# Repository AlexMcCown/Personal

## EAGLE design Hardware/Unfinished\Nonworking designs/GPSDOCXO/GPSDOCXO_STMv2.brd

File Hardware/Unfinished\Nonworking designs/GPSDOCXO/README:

Im starting to upload old designs that i never finished.
This is an GPSDOCXO or GPS Disciplined Oven-Controlled crystal(X) Oscillator to be used as a 10MHz lab reference.
The basic design is simple, a good oven-controlled crystal oscillator like the double oven used here is capable of drift and jitter down in the parts per billion but is not very accurate
A GPS based time reference is extremely accurate but not at a usable frequency.
GPSDOCXO's are designed to lock an OCXO to a timing GPS.

My concept was a mix of a PLL (phase locked loop) and a FLL (frequency locked loop) with the basic concept working in 2 stages.
Stage 1 is the FLL stage, we lock the OCXO to the 1 PPS (pulse per second) signal of the GPS, we start by counting the number of pulses the OCXO puts out between 2 rising edges of the GPS PPS.
We adjust our OCXO using a look up table or formula to match the desired frequency and try again, once thats locked we increase our gate time to 10 pulses, and count.
we continue this for as much as a 425 gates (or roughly 7 minutes) and adjust.
Once we have reached lock we can slowly skew the OCXO until we are right on the edge of going one count over, this will keep our phases locked.
As double oven OCXOs should never be turned off once burned in, this long startup time is fine.

The hardware is fairly simple, we convert the sine wave from the OCXO to a square wave using a TLV3501 4.5-ns compactor, that is fed in to a PL123-05N clock distribution chip that
claims 60fs of RMS jitter. The output of that is split in to 3 usable output ports (2 of them are 50 ohm buffered) with one going to a MAXII CPLD (Complex programmable logic device)
that handles the counting and reports the count offset (no need to report the full count as it will be close enough) to an STM32F402CC based USB module, that module controls a 
DACx0501 (i indend to use a DAC80501 here) that has a 5-ppm/˚C class voltage reference built in. 
The GPS used is a Ublox LEA-5T-0-003 based timing GPS module thats avalable on ebay for under $20 removed from huawei 4G cell towers.
These modules are very nice as they come with built in TVS suppressors, antenna power injection and over current detection.
This whole design was designed to fit in to standard aluminum extrusion cases.

There are plenty of issues with this design. First of all the CPLD code is rough and unfinished. The 2 layer PCB was a pipe-dream and is simply too few layers for this sort of design
in this sort of size.
The OCXO unit will need to be placed in a separate box as the unit it self can easily hit 50*C and bake everything inside.
There is no on board primary power supply.
There is a bottleneck somewhere in the design but without building it im not sure where it is. Obviously this is not 100% perfectly accurate and precise of a 10MHz time reference 
something has to be the bottleneck.  If the bottleneck is the OCXO or the GPS we can reduce part cost. Either use cheaper clock distributors, a lower resolution DAC or using a
single cheap FPGA to replace the microcontroller entirely. Normally i will create a design with the best chips i can than reduce part specifications until we approch our bottleneck.
Having a GPS on board means that this design is ideal for not just being a GPSDOCXO but also an NTP server, using a microcontroller with ethernet like an LPC1768 might be a better
solution.
a single 5v line on the PCB is unconnected and a re-layout of the upper right section is required.
The STM32F402CC board is not a standard blackpill and does not have an easy name to reference people to.
The STM32F402CC is only used for its USB and Floating point unit.
There is no font panel PCB but the intention was 5 buttons and an OLED display.

I might come back to this design but with access to a high precision atomic frequency counter, simply using my OCXO as a routinely calabrated unit is good enough for my home use.

The CPLD code is written in verilog, does not include a functional Shift-Out register and was the first time i have written anything in verilog. The only solution i could come up with
for the problem of resetting a counter while continiously counting was to create 2 counters.  This should all fit in the smallest MAX II CPLD so i left it like that.
There is an external GPIO interface intended for a distribution box, Internal header intended for an FTP server, The front RS232 is for standard NMEA output, configuration or the FTP
depending on jumper configurations.

EDIT: There is no code for the STM32F402CC.  I started writing it in C++ than switched over to platformio/arduino and chose to stop until i had the actual hardware in hand.
If i can find any of it i will upload both here.  The only thing i implemented were some test scripts to write to the CPLD and read, controlling the DAC and reading from the GPS.

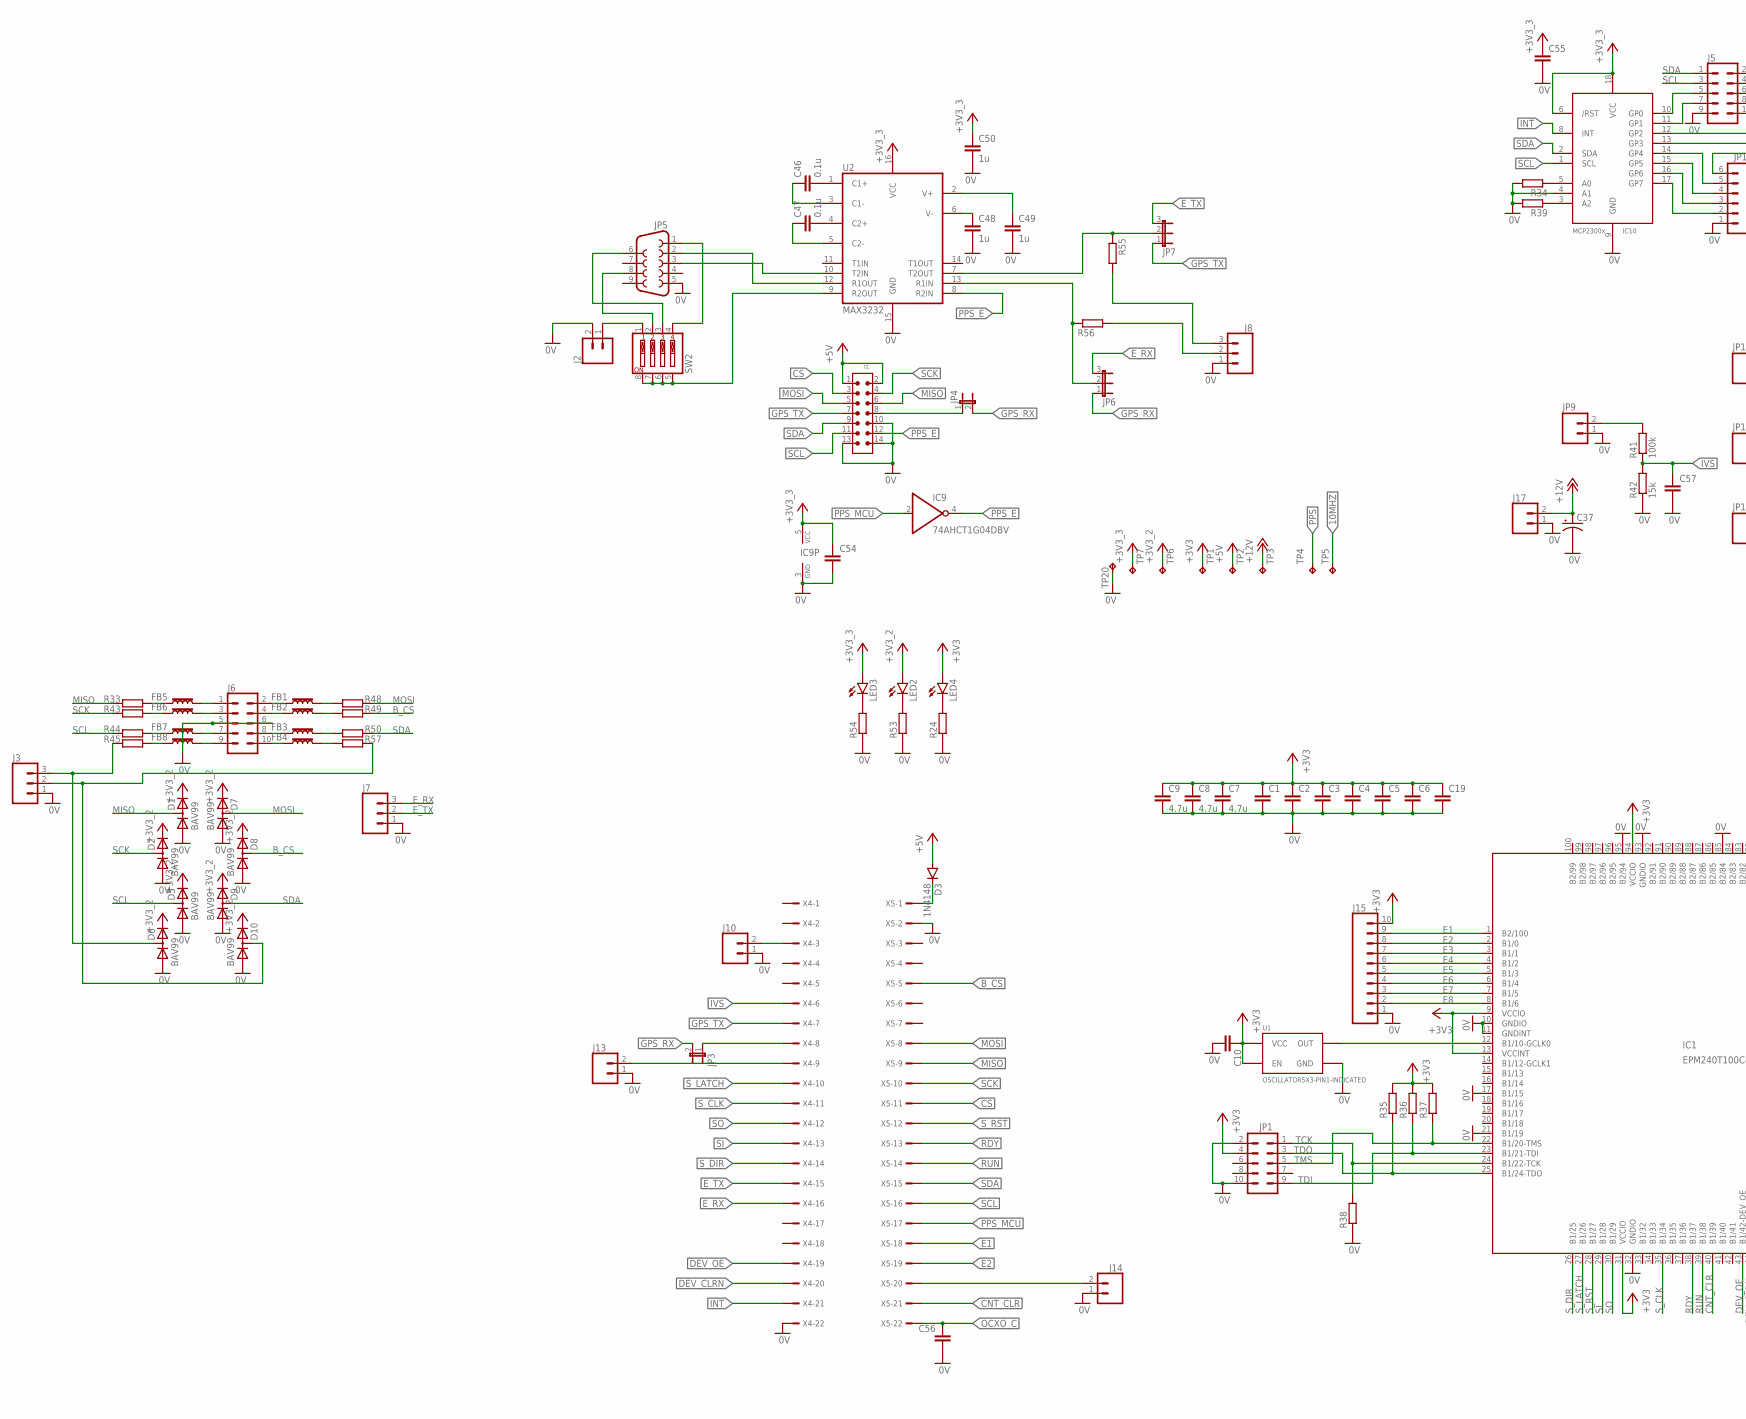
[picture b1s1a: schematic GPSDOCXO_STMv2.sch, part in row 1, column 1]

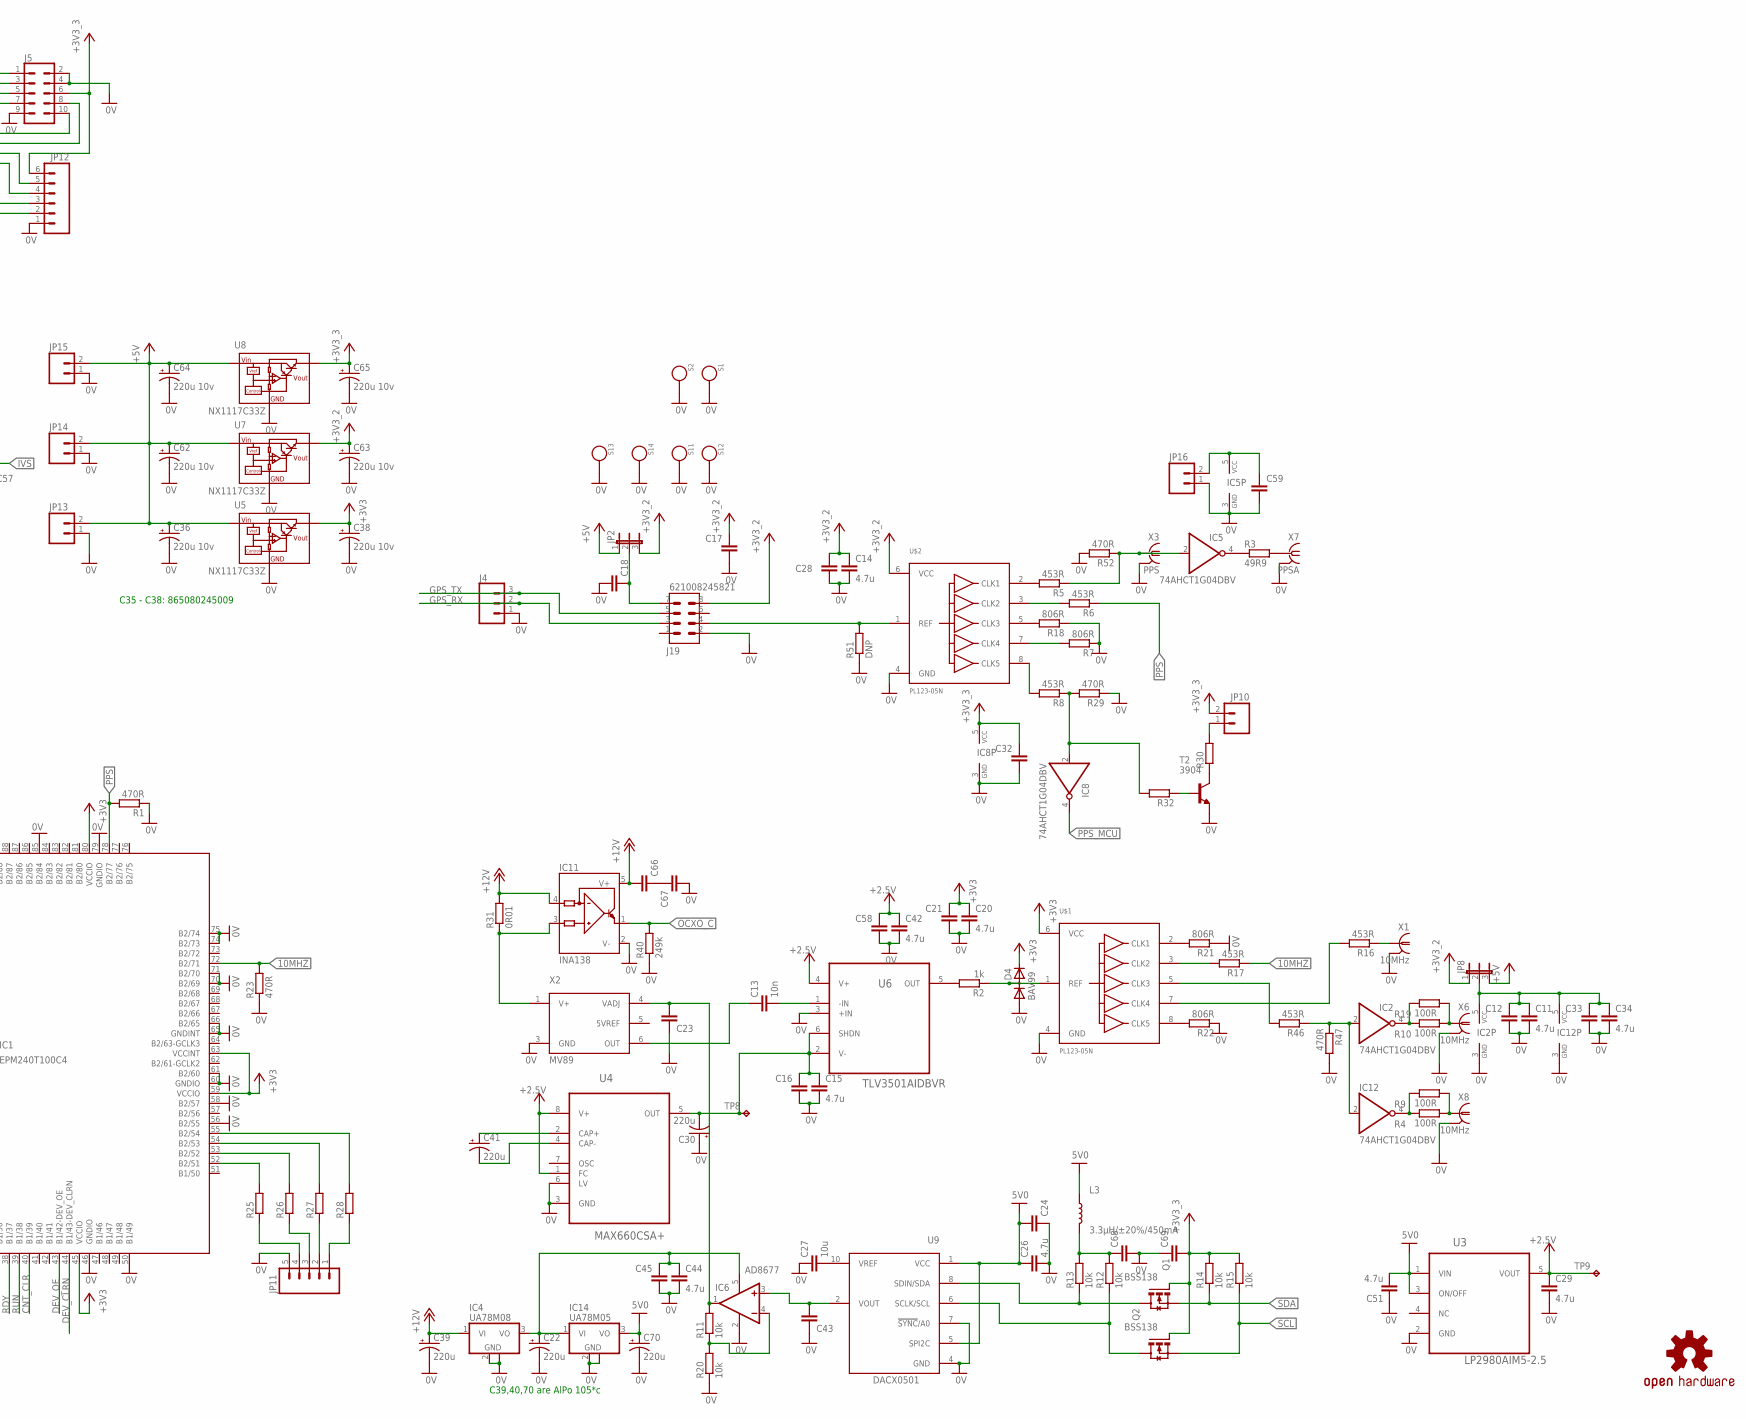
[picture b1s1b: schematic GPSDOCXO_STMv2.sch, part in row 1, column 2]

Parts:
C1, C2, C3, C4, C5, C6, C10, C12, C16, C19, C21, C23, C24, C28, C32, C33, C43, C45, C54, C55, C56, C57, C58, C59, C66, C67, C68, C69: C-EUC0603; C0603
C7, C8, C9, C11, C14, C15, C20, C26, C29, C34, C42, C44, C51: 4.7u; C0805
C13: 10n; C0805
C17, C18: C-EUC0805; C0805
C22, C70: 220u; 153CLV-0605
C27: 10u; C0805
C30, C39, C41: 220u; 153CLV-1010
C36, C38, C62, C63, C64, C65: 220u 10v; 153CLV-0605
C37: CPOL-USE3.5-8; E3,5-8
C46, C47: 0.1u; C0603
C48, C49, C50: 1u; C0603
D1, D2, D4, D5, D6, D7, D8, D9, D10: BAV99; SOT23
D3: 1N4148; DO35-7
FB1, FB2, FB3, FB4, FB5, FB6, FB7, FB8: FERRITE_BEAD-0603; 0603
IC1: EPM240T100C4; TQFP100
IC2, IC5, IC8, IC9, IC12: 74AHCT1G04DBV; SOT23-5
IC4: UA78M08; SOT223
IC6: AD8677; SOT23-5
IC10: MCP23008/SO; SO18W
IC11: INA138; SOT23-5
IC14: UA78M05; SOT223
J1: 6120XX21621_61201421621; 61201421621
J2, J10, J13, J14: CONN_02; 1X02
J3, J7, J8: M03POLAR; MOLEX-1X3
J4: CONN_03; 1X03
J5: CONN_05X2SHD-NS; 2X5-SHROUDED-NS
J6: CONN_05X2RAF; 2X5-RAF
J15: CONN_10NO_SILK_PTH_FEMALE; 1X10_NO_SILK
J17: CONN_025MM; SCREWTERMINAL-5MM-2
J19: 621008245821
JP1: M05X2SHD-NS; 2X5-SHROUDED-NS
JP2, JP6, JP7, JP8: JP2E; JP2
JP3, JP4: JP1E; JP1
JP5: DB9FEMALE; DB9
JP9, JP10, JP13, JP14, JP15, JP16: M02POLAR; MOLEX-1X2
JP11: M05NO_SILK; 1X05_NO_SILK
JP12: M06SILK_FEMALE_PTH; 1X06
L3: 3.3µH/±20%/450mA; 0805
LED2, LED3, LED4: LED5MM
LOGO1: OSHW-LOGOL; OSHW-LOGO-L
Q1, Q2: BSS138; SOT23-3
R1, R23, R29, R47, R52: 470R; R0603
R2: 1k; R0603
R3: 49R9; R0805
R4, R9, R10, R19: 100R; R0805
R5, R6, R8, R16, R17, R46: 453R; R0603
R7, R18, R21, R22: 806R; R0603
R11, R12, R13, R14, R15, R20: 10k; R0603
R24, R25, R26, R27, R28, R30, R32, R33, R34, R35, R36, R37, R38, R39, R43, R44, R45, R48, R49, R50, R53, R54, R55, R56, R57: R-EU_R0603; R0603
R31: 0R01; R1210
R40: 249k; R0603
R41: 100k; 0204/7
R42: 15k; R0603
R51: DNP; R0603
S1, S2, S11, S12, S13, S14: STANDOFF_ELECTRICAL; STANDOFF-ELECTRICAL
SW2: SW_DIP-4; EDG-04
T2: 3904; SOT23-BEC
TP1, TP2, TP3, TP6, TP7, TP8, TP9, TP20: TPPAD1-13; P1-13
TP4, TP5: TPTP13R; TP13R
U1: OSCILLATOR5X3-PIN1-INDICATED; CRYSTAL-OSC-SMD-5X3
U2: MAX3232; SO16
U3: LP2980AIM5-2.5; SOT95P284X119-5N
U4: MAX660CSA+; SOIC127P600X175-8N
U5, U7, U8: NX1117C33Z; SOT223
U6: TLV3501AIDBVR; SOT95P280X145-6N
U9: DACX0501; VSSOP-10
U$1, U$2: PL123-05N; SOIC-8
X1, X6, X8: 10MHz; AMP_227161
X2: MV89
X3: PPS; BU-SMA-V
X4, X5: TSW-122-07-G-S; TSW-122-XX-G-S
X7: PPSA; BU-SMA-V

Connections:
0V: C1.2, C2.2, C3.2, C4.2, C5.2, C6.2, C7.2, C8.2, C9.2, C10.2, C11.2, C12.2, C14.2, C15.2, C16.2, C17.2, C18.2, C19.2, C20.2, C21.2, C22.-, C23.1, C24.1, C26.2, C27.1, C28.2, C29.2, C30.+, C32.2, C33.2, C34.2, C36.-, C37.-, C38.-, C39.-, C42.2, C43.1, C44.2, C45.2, C48.2, C49.2, C50.2, C51.1, C54.2, C55.2, C56.2, C57.2, C58.2, C59.2, C62.-, C63.-, C64.-, C65.-, C67.2, C68.1, C69.2, C70.-, D1.1 (A1), D2.1 (A1), D4.1 (A1), D5.1 (A1), D6.1 (A1), D7.1 (A1), D8.1 (A1), D9.1 (A1), D10.1 (A1), IC1.10 (GNDIO), IC1.11 (GNDINT), IC1.17 (B1/15), IC1.21 (B1/19), IC1.32 (GNDIO), IC1.46 (GNDIO), IC1.50 (B1/49), IC1.56 (B2/55), IC1.58 (B2/57), IC1.60 (GNDIO), IC1.61 (B2/60), IC1.65 (GNDINT), IC1.66 (B2/65), IC1.70 (B2/69), IC1.71 (B2/70), IC1.74 (B2/73), IC1.75 (B2/74), IC1.79 (GNDIO), IC1.85 (B2/84), IC1.93 (GNDIO), IC1.95 (B2/94), IC2.3 (GND), IC4.2 (GND), IC4.4 (GND), IC5.3 (GND), IC6.2 (V-), IC8.3 (GND), IC9.3 (GND), IC10.4 (A1), IC10.9 (GND), IC11.2 (V-), IC12.3 (GND), IC14.2 (GND), IC14.4 (GND), J1.10, J1.13, J1.14, J2.2, J3.1, J4.1, J5.2, J5.4, J5.9, J6.5, J6.6, J7.1, J8.1, J10.1, J13.1, J14.1, J15.1, J17.1, J19.2, JP1.2, JP1.10, JP5.5, JP9.1, JP11.5, JP12.1, JP13.1, JP14.1, JP15.1, JP16.1, R1.1, R7.1, R18.1, R20.1, R21.1, R22.1, R23.1, R24.1, R29.1, R34.2, R38.1, R39.2, R40.1, R42.1, R47.2, R51.1, R52.2, R53.1, R54.1, S1.P1, S2.P1, S11.P1, S12.P1, S13.P1, S14.P1, T2.E, TP20.TP, U1.2 (GND), U2.15 (GND), U3.2 (GND), U4.3 (GND), U4.6 (LV), U5.1 (GND), U6.3 (+IN), U7.1 (GND), U8.1 (GND), U9.4 (GND), U9.7 (!SYNC!/A0), U$1.4 (GND), U$2.4 (GND), X1.2, X2.3 (GND), X3.2, X3.3 (2), X3.4 (2), X3.5 (2), X4.22, X5.2, X6.2, X7.2, X7.3 (2), X7.4 (2), X7.5 (2), X8.2
10MHZ: IC1.72 (B2/71), R17.1, R23.2, TP5.TP
+2V5: C29.1, C42.1, C58.1, TP9.TP, U3.5 (VOUT), U4.1 (FC), U4.8 (V+), U6.4 (V+)
+3V3: C1.1, C2.1, C3.1, C4.1, C5.1, C6.1, C7.1, C8.1, C9.1, C10.1, C19.1, C20.1, C21.1, C38.+, D4.2 (K2), IC1.9 (VCCIO), IC1.13 (VCCINT), IC1.31 (VCCIO), IC1.45 (VCCIO), IC1.59 (VCCIO), IC1.63 (VCCINT), IC1.80 (VCCIO), IC1.94 (VCCIO), J15.10, JP1.4, LED4.A, R35.2, R36.2, R37.2, TP1.TP, U1.1 (EN), U1.4 (VCC), U5.2 (VOUT), U5.4 (VOUT), U$1.6 (VCC)
+3V3_2: C14.1, C17.1, C28.1, C63.+, D1.2 (K2), D2.2 (K2), D5.2 (K2), D6.2 (K2), D7.2 (K2), D8.2 (K2), D9.2 (K2), D10.2 (K2), J19.8, JP2.3, JP8.1, LED2.A, TP6.TP, U7.2 (VOUT), U7.4 (VOUT), U$2.6 (VCC)
+3V3_3: C32.1, C50.1, C54.1, C55.1, C65.+, C69.1, IC8.5 (VCC), IC9.5 (VCC), IC10.6 (/RST), IC10.18 (VCC), J5.6, JP10.2, JP12.6, LED3.A, Q1.1 (G), Q2.1 (G), R14.2, R15.2, TP7.TP, U2.16 (VCC), U8.2 (VOUT), U8.4 (VOUT)
+5V: C36.+, C62.+, C64.+, D3.A, J1.1, J1.2, JP2.1, JP8.3, JP13.2, JP14.2, JP15.2, TP2.TP, U5.3 (VIN), U7.3 (VIN), U8.3 (VIN)
+12V: C37.+, C39.+, C66.2, IC4.1 (VI), IC11.4 (IN-), IC11.5 (V+), J17.2, R31.2, TP3.TP
+V: C24.2, C26.1, C51.2, C70.+, IC14.3 (VO), L3.1, U3.1 (VIN), U3.3 (ON/OFF), U9.1 (VCC), U9.5 (SPI2C)
B_CS: D8.3 (K1A2), R49.1, X5.5
CNT_CLR: IC1.40 (B1/39), X5.21
CS: J1.3, X5.11
DEV_CLRN: IC1.44 (B1/43-DEV_CLRN), X4.20
DEV_OE: IC1.43 (B1/42-DEV_OE), X4.19
E1: IC1.1 (B2/100), J15.9, X5.18
E2: IC1.2 (B1/0), J15.8, X5.19
E3: IC1.3 (B1/1), J15.7
E4: IC1.4 (B1/2), J15.6
E5: IC1.5 (B1/3), J15.5
E6: IC1.6 (B1/4), J15.4
E7: IC1.7 (B1/5), J15.3
E8: IC1.8 (B1/6), J15.2
E_RX: J7.3, JP6.3, X4.16
E_TX: J7.2, JP7.3, X4.15
GPS_RX: J4.2, J19.3, JP3.2, JP4.2, JP6.1
GPS_RX_AJ: JP3.1, X4.8
GPS_RX_AJ2: J1.8, JP4.1
GPS_TX: J1.7, J4.3, J19.5, JP7.1, X4.7
INT: IC10.8 (INT), X4.21
IVS: C57.1, R41.1, R42.2, X4.6
MISO: D1.3 (K1A2), J1.6, R33.1, X5.9
MOSI: D7.3 (K1A2), J1.5, R48.1, X5.8
unnamed: J13.2, X4.9
unnamed: JP9.2, R41.2
unnamed: J19.4, R51.2, U$2.1 (REF)
unnamed: R5.2, U$2.2 (CLK1)
unnamed: C13.2, U6.1 (-IN)
unnamed: C13.1, X2.6 (OUT)
unnamed: R21.2, U$1.2 (CLK1)
unnamed: JP7.2, R55.1, U2.7 (T2OUT)
unnamed: R6.2, U$2.3 (CLK2)
unnamed: R7.2, U$2.7 (CLK4)
unnamed: JP5.2, U2.12 (R1OUT)
unnamed: R18.2, U$2.5 (CLK3)
unnamed: R8.2, U$2.8 (CLK5)
unnamed: IC10.10 (GP0), J5.5
unnamed: R32.1, T2.B
unnamed: JP10.1, R30.2
unnamed: R30.1, T2.C
unnamed: R2.2, U6.5 (OUT)
unnamed: IC1.12 (B1/10-GCLK0), U1.3 (OUT)
unnamed: C23.2, IC6.1 (OUT), R11.2, X2.4 (VADJ)
unnamed: IC5.4 (O), R3.1
unnamed: C22.+, C44.1, C45.1, IC4.3 (VO), IC6.5 (V+), IC14.1 (VI)
unnamed: Q1.3 (D), R13.1, U9.8 (SDIN/SDA)
unnamed: IC12.4 (O), R4.1, R9.1
unnamed: IC5.2 (I), R5.1, R52.1, X3.1
unnamed: Q2.3 (D), R12.1, U9.6 (SCLK/SCL)
unnamed: R3.2, X7.1
unnamed: R4.2, R9.2, X8.1
unnamed: J8.2, R56.2
unnamed: C18.1, J19.7, JP2.2
unnamed: J10.2, X4.3
unnamed: C66.1, C67.1
unnamed: IC10.11 (GP1), J5.7
unnamed: IC10.12 (GP2), J5.10
unnamed: IC10.13 (GP3), J5.8
unnamed: IC10.16 (GP6), JP12.3
unnamed: R17.2, U$1.3 (CLK2)
unnamed: R46.2, U$1.5 (CLK3)
unnamed: IC10.14 (GP4), JP12.5
unnamed: IC10.15 (GP5), JP12.4
unnamed: IC10.17 (GP7), JP12.2
unnamed: IC10.5 (A0), R34.1
unnamed: LED4.K (C), R24.2
unnamed: JP11.4, R25.1
unnamed: IC10.3 (A2), R39.1
unnamed: JP11.3, R26.1
unnamed: JP11.2, R27.1
unnamed: JP11.1, R28.1
unnamed: IC1.52 (B2/51), R25.2
unnamed: IC1.53 (B2/52), R26.2
unnamed: IC1.54 (B2/53), R27.2
unnamed: IC1.55 (B2/54), R28.2
unnamed: IC2.2 (I), IC12.2 (I), R46.1, R47.1
unnamed: C11.1, C12.1, C33.1, C34.1, IC2.5 (VCC), IC12.5 (VCC), JP8.2
unnamed: C59.1, IC5.5 (VCC), JP16.2
unnamed: IC6.4 (-IN), R11.1, R20.2
unnamed: C68.2, L3.2, R12.2, R13.2
unnamed: J8.3, R55.2
unnamed: IC2.4 (O), R10.1, R19.1
unnamed: C43.2, IC6.3 (+IN), U9.2 (VOUT)
unnamed: J14.2, X5.20
unnamed: JP5.3, U2.10 (T2IN)
unnamed: C27.2, U9.10 (VREF)
unnamed: FB5.2, J6.1
unnamed: J2.1, SW2.1
unnamed: IC8.2 (I), R8.1, R29.2, R32.2
unnamed: IC11.3 (IN+), R31.1, X2.1 (V+)
unnamed: FB6.2, J6.3
unnamed: JP5.1, SW2.4
unnamed: FB7.2, J6.7
unnamed: FB8.2, J6.9
unnamed: FB1.1, J6.2
unnamed: FB2.1, J6.4
unnamed: JP6.2, R56.1, U2.13 (R1IN)
unnamed: R16.2, U$1.7 (CLK4)
unnamed: JP5.8, SW2.2
unnamed: LED2.K (C), R53.2
unnamed: D4.3 (K1A2), R2.1, U$1.1 (REF)
unnamed: R10.2, R19.2, X6.1
unnamed: C15.1, C16.1, C30.-, TP8.TP, U4.5 (OUT), U6.2 (V-), U6.6 (SHDN)
unnamed: C41.+, U4.2 (CAP+)
unnamed: C41.-, U4.4 (CAP-)
unnamed: LED3.K (C), R54.2
unnamed: D3.C, X5.1
unnamed: FB3.1, J6.8
unnamed: FB4.1, J6.10
unnamed: R22.2, U$1.8 (CLK5)
unnamed: FB1.2, R48.2
unnamed: JP5.6, SW2.3
unnamed: FB2.2, R49.2
unnamed: FB3.2, R50.2
unnamed: FB4.2, R57.2
unnamed: FB5.1, R33.2
unnamed: FB6.1, R43.2
unnamed: R16.1, X1.1
unnamed: SW2.5, SW2.6, SW2.7, SW2.8, U2.9 (R2OUT)
unnamed: C46.2, U2.1 (C1+)
unnamed: C47.2, U2.4 (C2+)
unnamed: C48.1, U2.6 (V-)
unnamed: C49.1, U2.2 (V+)
unnamed: C46.1, U2.3 (C1-)
unnamed: C47.1, U2.5 (C2-)
unnamed: FB7.1, R44.2
unnamed: FB8.1, R45.2
unnamed: D6.3 (K1A2), J3.3, R45.1
unnamed: D10.3 (K1A2), J3.2, R57.1
OCXO_C: C56.1, IC11.1 (OUT), R40.2, X5.22
PPS: IC1.78 (B2/77), R1.2, R6.1, TP4.TP
PPS_E: IC9.4 (O), J1.12, U2.8 (R2IN)
PPS_MCU: IC8.4 (O), IC9.2 (I), X5.17
RDY: IC1.38 (B1/37), X5.13
RUN: IC1.39 (B1/38), X5.14
SCK: D2.3 (K1A2), J1.4, R43.1, X5.10
SCL: D5.3 (K1A2), IC10.1 (SCL), J1.11, J5.3, Q2.2 (S), R15.1, R44.1, X5.16
SDA: D9.3 (K1A2), IC10.2 (SDA), J1.9, J5.1, Q1.2 (S), R14.1, R50.1, X5.15
SI: IC1.29 (B1/28), X4.13
SO: IC1.30 (B1/29), X4.12
S_CLK: IC1.35 (B1/34), X4.11
S_DIR: IC1.26 (B1/25), X4.14
S_LATCH: IC1.27 (B1/26), X4.10
S_RST: IC1.28 (B1/27), X5.12
TCK: IC1.24 (B1/22-TCK), JP1.1, R38.2
TDI: IC1.23 (B1/21-TDI), JP1.9, R36.1
TDO: IC1.25 (B1/24-TDO), JP1.3, R35.1
TMS: IC1.22 (B1/20-TMS), JP1.5, R37.1

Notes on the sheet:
C35 - C38: 865080245009
C39,40,70 are AlPo 105*c

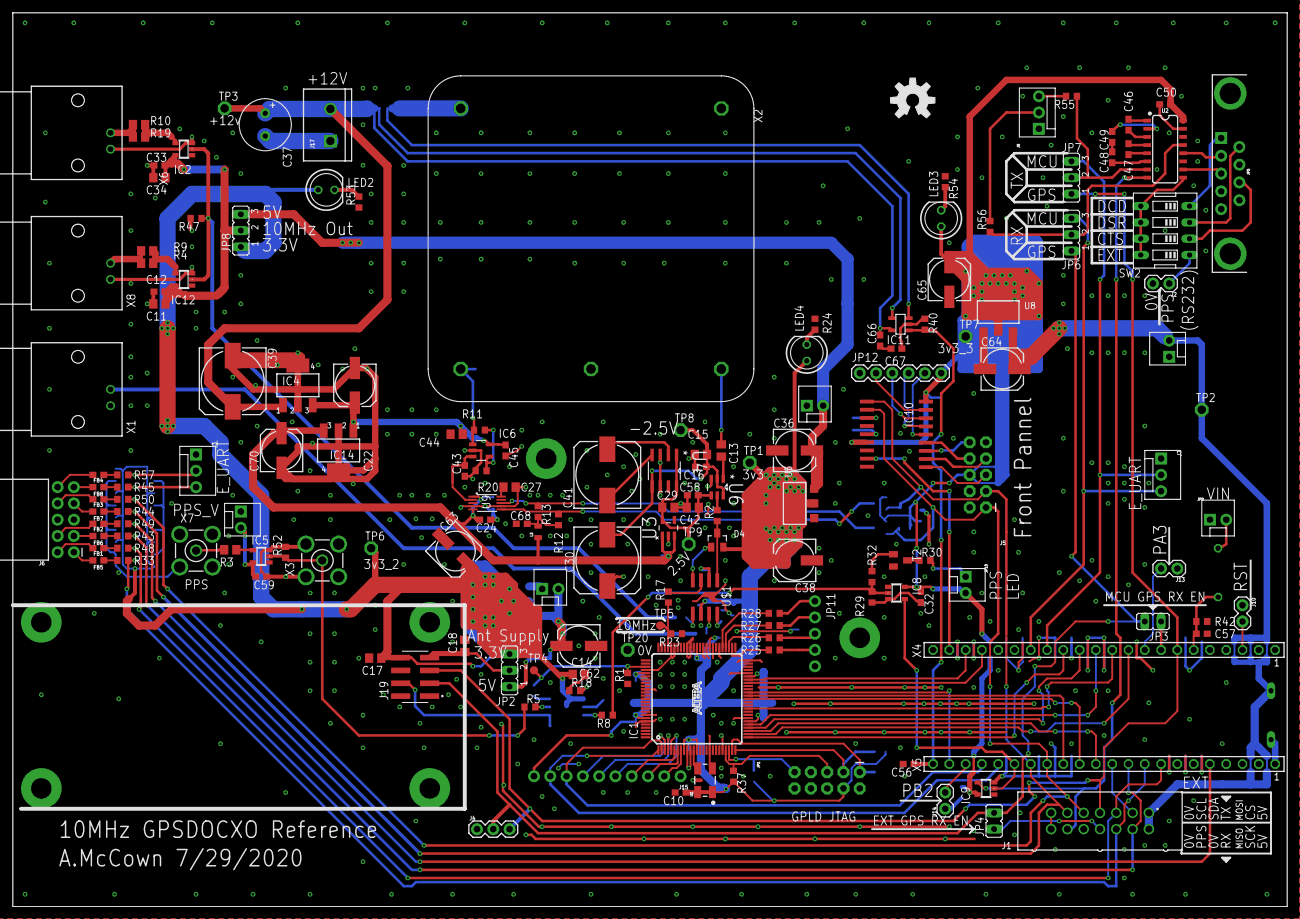
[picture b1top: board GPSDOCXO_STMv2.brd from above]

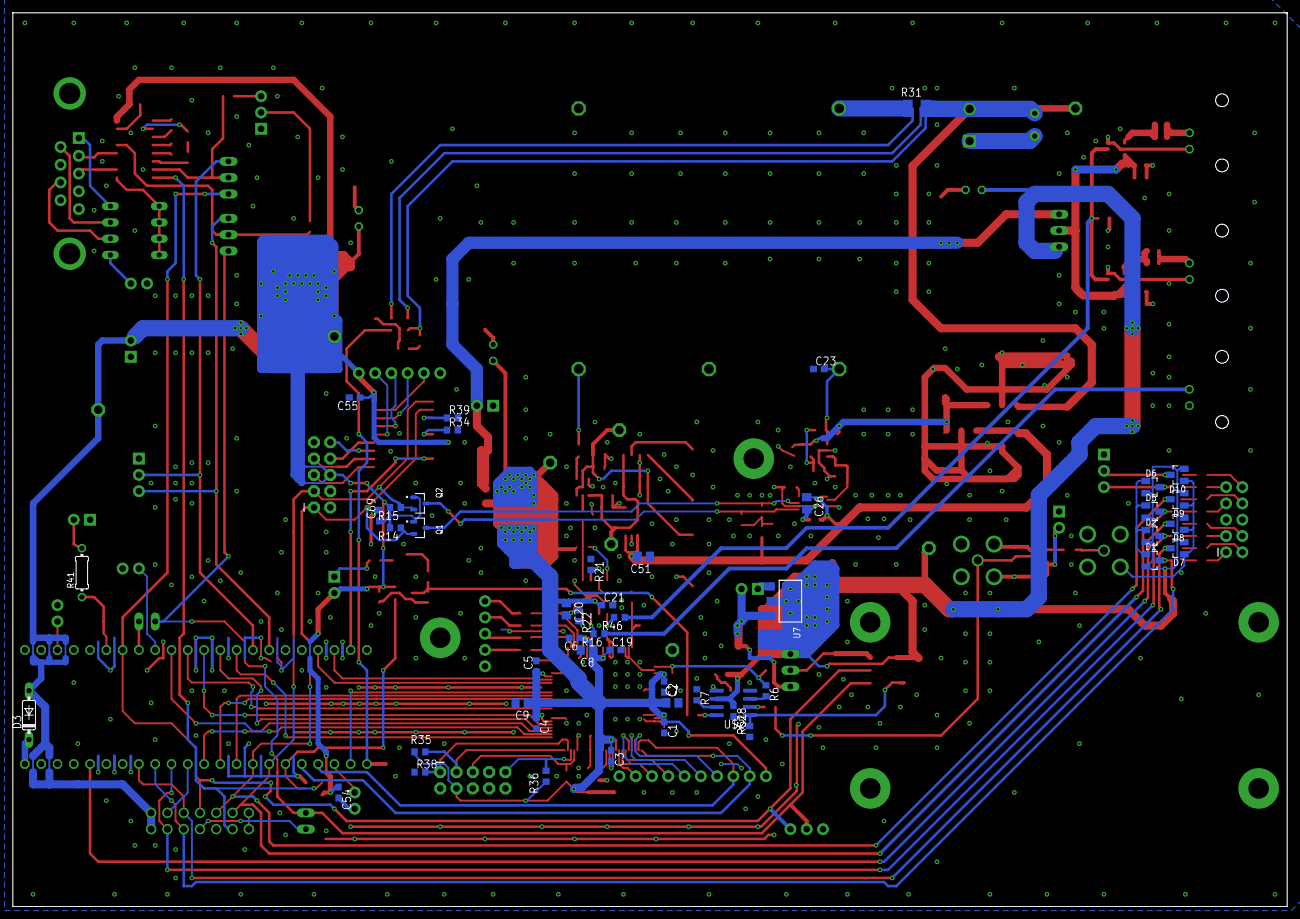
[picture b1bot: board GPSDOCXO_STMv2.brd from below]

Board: 2 copper layers, 198.7 x 139.4 mm, 222 parts (48 on the bottom side), 157 nets.

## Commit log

2021-03-24 Rename Arduino/Arduino/ESP32 SPI Slave Read Only/README to Arduino/ESP32/SPI Slave Read Only/README
2021-03-24 Rename Arduino/Arduino/ESP32 SPI Slave Read Only/bitbang.ino to Arduino/ESP32/SPI Slave Read/Onlybitbang.ino
2021-03-24 Rename Arduino/ESP32/SPI Slave Read Only/README to Arduino/ESP32/SPI Slave Read/README
2021-12-18 Create LEDMatrixImgGen.py
    Created in about an hour to help a friend make textures for a 3D project, it functions simply, you provide it with information such as the input image, size of the resulting image in pixels, number o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
    it will produce an output PNG that looks similar to an LED matrix, full color and represents the input file.
    This code is unoptimized and was written in one sitting to do one task rapidly using libraries that i knew off the top of my head. I might revisit this if there is interest.

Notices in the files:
parts and their libraries:
NXP_60_26022015: This library may be distributed and adapted freely for any purpose, as long as NXP is credited and any new creation is licensed under the same terms.
Wurth_Connectors_WR-BHD: Copyright: Würth Elektronik
